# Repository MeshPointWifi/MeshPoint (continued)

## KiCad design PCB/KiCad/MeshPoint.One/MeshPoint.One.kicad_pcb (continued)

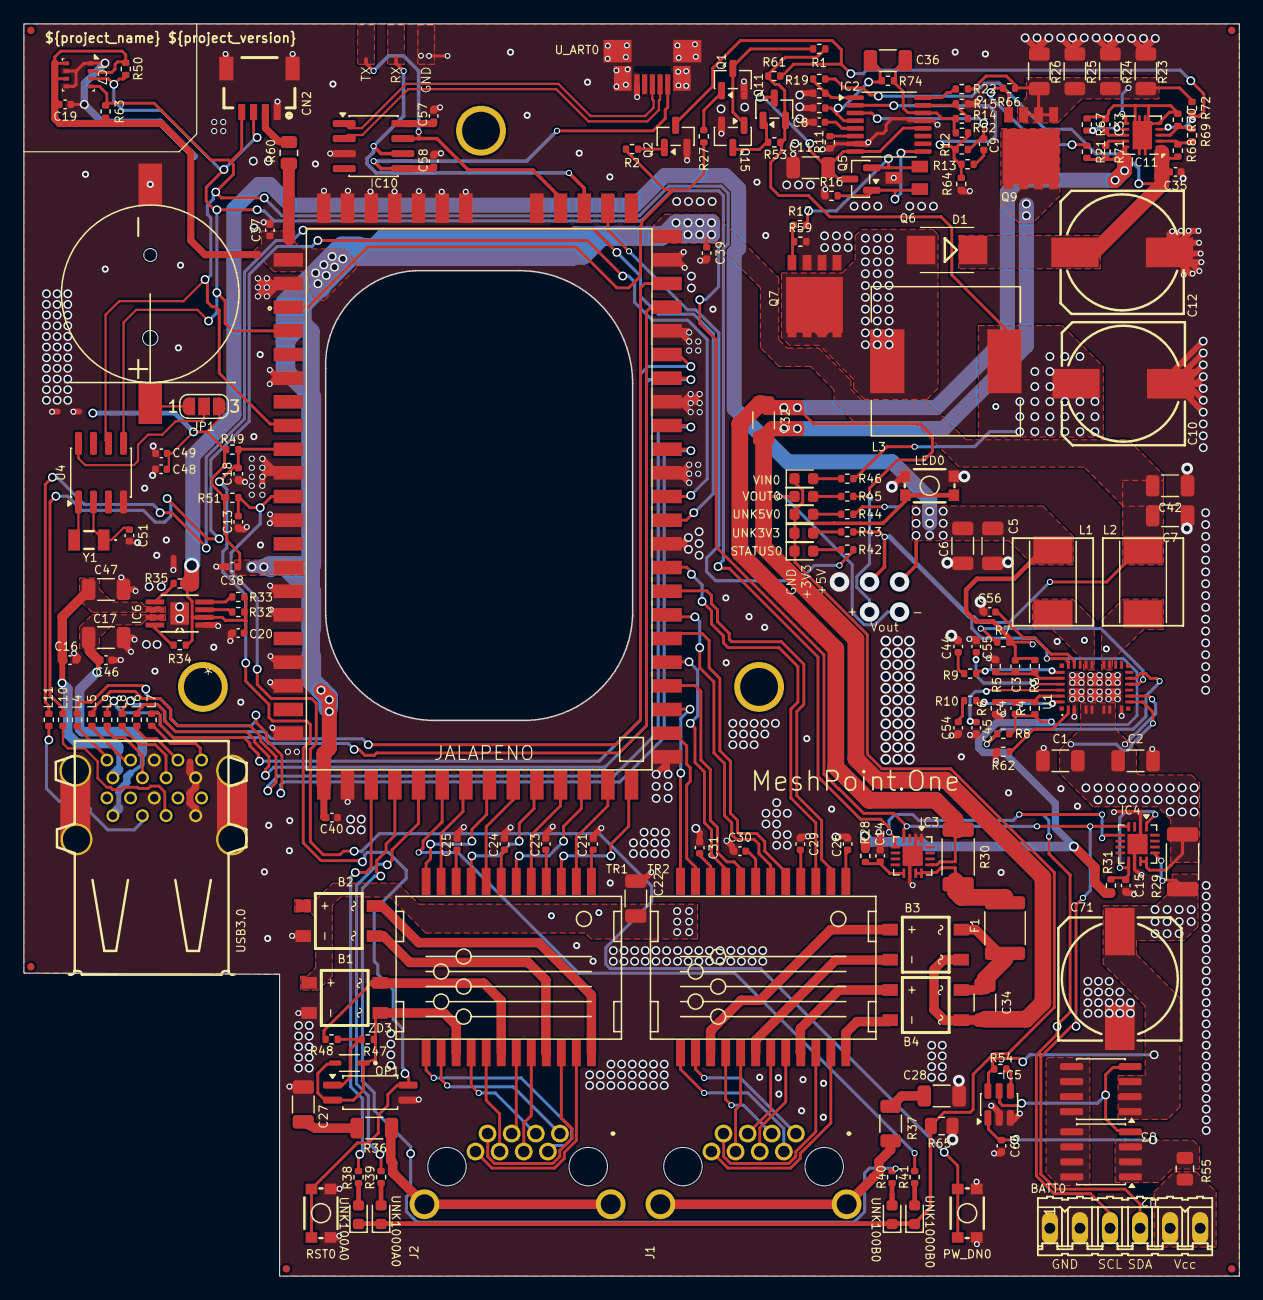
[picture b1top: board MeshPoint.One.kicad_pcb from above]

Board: 4 copper layers, 102.6 x 105.7 mm, 194 parts (1 on the bottom side), 165 nets.

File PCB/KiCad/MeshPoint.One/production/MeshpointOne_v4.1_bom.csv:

Designator,Footprint,Quantity,Value,LCSC Part #
"B1, B2, B3, B4",MBS,4,1A/50V,C2488
BATT1,BATERIJA12MM,1,BATTCR1220,C70377
"C1, C2",1206,2,4.7uF,C29823
"C10, C12, C71",153CLV-1010,3,220u/35V,C178562
"C11, C17, C22, C32, C34, C47",1206,6,10u/35V,C13585
"C13, C18",0402,2,100p/35V,C1546
"C14, C15, C35, C66",0402,4,1u/35V,C307413
"C16, C19, C20, C21, C23, C24, C25, C26, C29, C30, C31, C40, C46, C48, C49, C57, C58",0402,17,100n/35V,C187828
"C27, C28",1206,2,10n/600V, C107201 
"C3, C4",0402,2,4.7pF,C1569
"C33, C8, C9",0402,3,10n/35V,C1524
C36,1206,1,47u/10V,C5448950
"C37, C38, C39",0402,3,100n,C187828
"C42, C5, C6, C7",1206,4,47uF,C96123
"C44, C45",0402,2,220pF,C1530 
C51,0402,1,22pF,C1555
"C54, C55",0402,2,10nF,C1524
C56,0402,1,1uF,C307413
CN2,EASYC,1,EASYC,C160404
D1,SMB,1,B140-13-F,C134426
F1,1812,1,2A,C70124
IC10,SOIC-8_3.9x4.9mm_P1.27mm,1,CH340N,C2977777
IC11,Texas_DRC0010J,1,TPS26623DRCR,C2155839
IC2,TSSOP-16_4.4x5mm_P0.65mm,1,TL494CPWR,C22396897
"IC3, IC4",QFN-16-1EP_3x3mm_P0.5mm_EP1.7x1.7mm,2,INA230_RGT_16,C882784
IC5,TSOT-23-6,1,LTC4412,C514442
IC6,DGN8_1P89X1P57,1,TPS2052B_DGN,C2879167
"J1, J2",SS60300079,2,SS-60300-079,C402283
"L1, L2",INDC6932X320,2,PA4333.102NLTPA4333.102NLT,C5151941
"L10, L11, L4, L5, L6, L7, L8, L9",0402,8,1nH,C19633897
L3,L_12x12mm_H6mm,1,22uH/1A,C2879697
LED0,TACTILE_SWITCH_SMD_4.6X2.8MM_535,1,MOMENTARY-SWITCH-SPST-SMD-4.6X2.8MM,C72443
OP1,SOP-4_4.4x2.6mm_P1.27mm,1,TLP283,C55144
PW_DN0,TACTILE_SWITCH_SMD_4.6X2.8MM_535,1,PW_DN,C72443
"Q1, Q15, Q2, Q5",SOT-23,4,BC847,C8664
Q11,SOT-23,1,SQ2319,C3280190
Q6,SOT23-BEC,1,BC857,C8549
"Q7, Q9",PG-TDSON-8,2,IRFH7932TRPBF,C51908847
"R1, R32, R33, R45, R50, R53, R59, R61, R63, R66, R73",0402,11,10k,C25744
"R10, R62, R9",0402,3,15k,C25756
"R11, R34, R35",0402,3,3.3k,C25890
R12,0402,1,150k,C25755
R13,0402,1,27K, C25771 
"R14, R52, R64",0402,3,51K,C25794
"R15, R22, R46, R48",0402,4,2K2,C25879
"R16, R20, R21",0402,3,1K,C11702
R17,0402,1,10R,C25077
R19,0402,1,8K2,C137929
"R2, R27, R49, R51",0402,4,4.7K,C25900
"R23, R24, R25, R26",1206,4,1R,C17928
"R28, R31",0402,2,1R,C25086
"R29, R30",2010,2,2mR,C844078
"R3, R4",0402,2,1M,C279988 
"R36, R37",1206,2,75R,C17987 
"R38, R39, R40, R41, R43",0402,5,330R,C25104
"R42, R44, R47",0402,3,470R,C25117
R5,0402,1,191k,C852583
"R54, R74",0402,2,470K,C25799
"R55, R60, R65",0805,3,0R,C17477
R6,0402,1,316k,C25777
R67,0402,1,13k3,C3015832
R68,0402,1,715k,C5126240
R69,0402,1,22K,C25768
"R7, R71, R72, R8",0402,4,100k,C25741
R70,0402,1,33K,"
C25779 "
RST0,TACTILE_SWITCH_SMD_4.6X2.8MM_535,1,RST,C72443
"STATUS0, VOUT0",0603,2,BL,C2288
"TR1, TR2",WURTH1000T,2,WURTH_TR,C6828534
U$5,JALAPENO-PCB,1,JALAPENO,
U1,QFN50P600X400X103-32N240X440,1,LT8650SEV#PBF,C3198284
"U2, U3",SOIC-8_3.9x4.9mm_P1.27mm,2,SI4435DYTRPBF,C67287
U4,SOIC-8_3.9x4.9mm_P1.27mm,1,PCF8563T,C7440
"UNK1000A0, UNK1000B0, UNK3V3, UNK5V0, VIN0",0603,5,GR,C72043
"UNK100A0, UNK100B0",0603,2,YL,C72038
USB3.0,USB3.0D,1,USB3.0D,
U_ART0,MOLEX-47364-0001,1,MOLEX-47346-0001,C232975
Y1,SC32S125PF20PPM,1,SC32S-12.5PF20PPM,C130253
ZD3,SOD2513X120N,1,BZT52C15S,C19077448

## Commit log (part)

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2017-01-27 Create LICENCE
2017-01-27 Added images
2017-01-27 renamed stl files
2017-05-22 added MeshPoint shell with MeshMixer supports added
2017-06-12 Removed nuts used for assembly, decreased hole diameter, reduced size of some parts for better fit.
